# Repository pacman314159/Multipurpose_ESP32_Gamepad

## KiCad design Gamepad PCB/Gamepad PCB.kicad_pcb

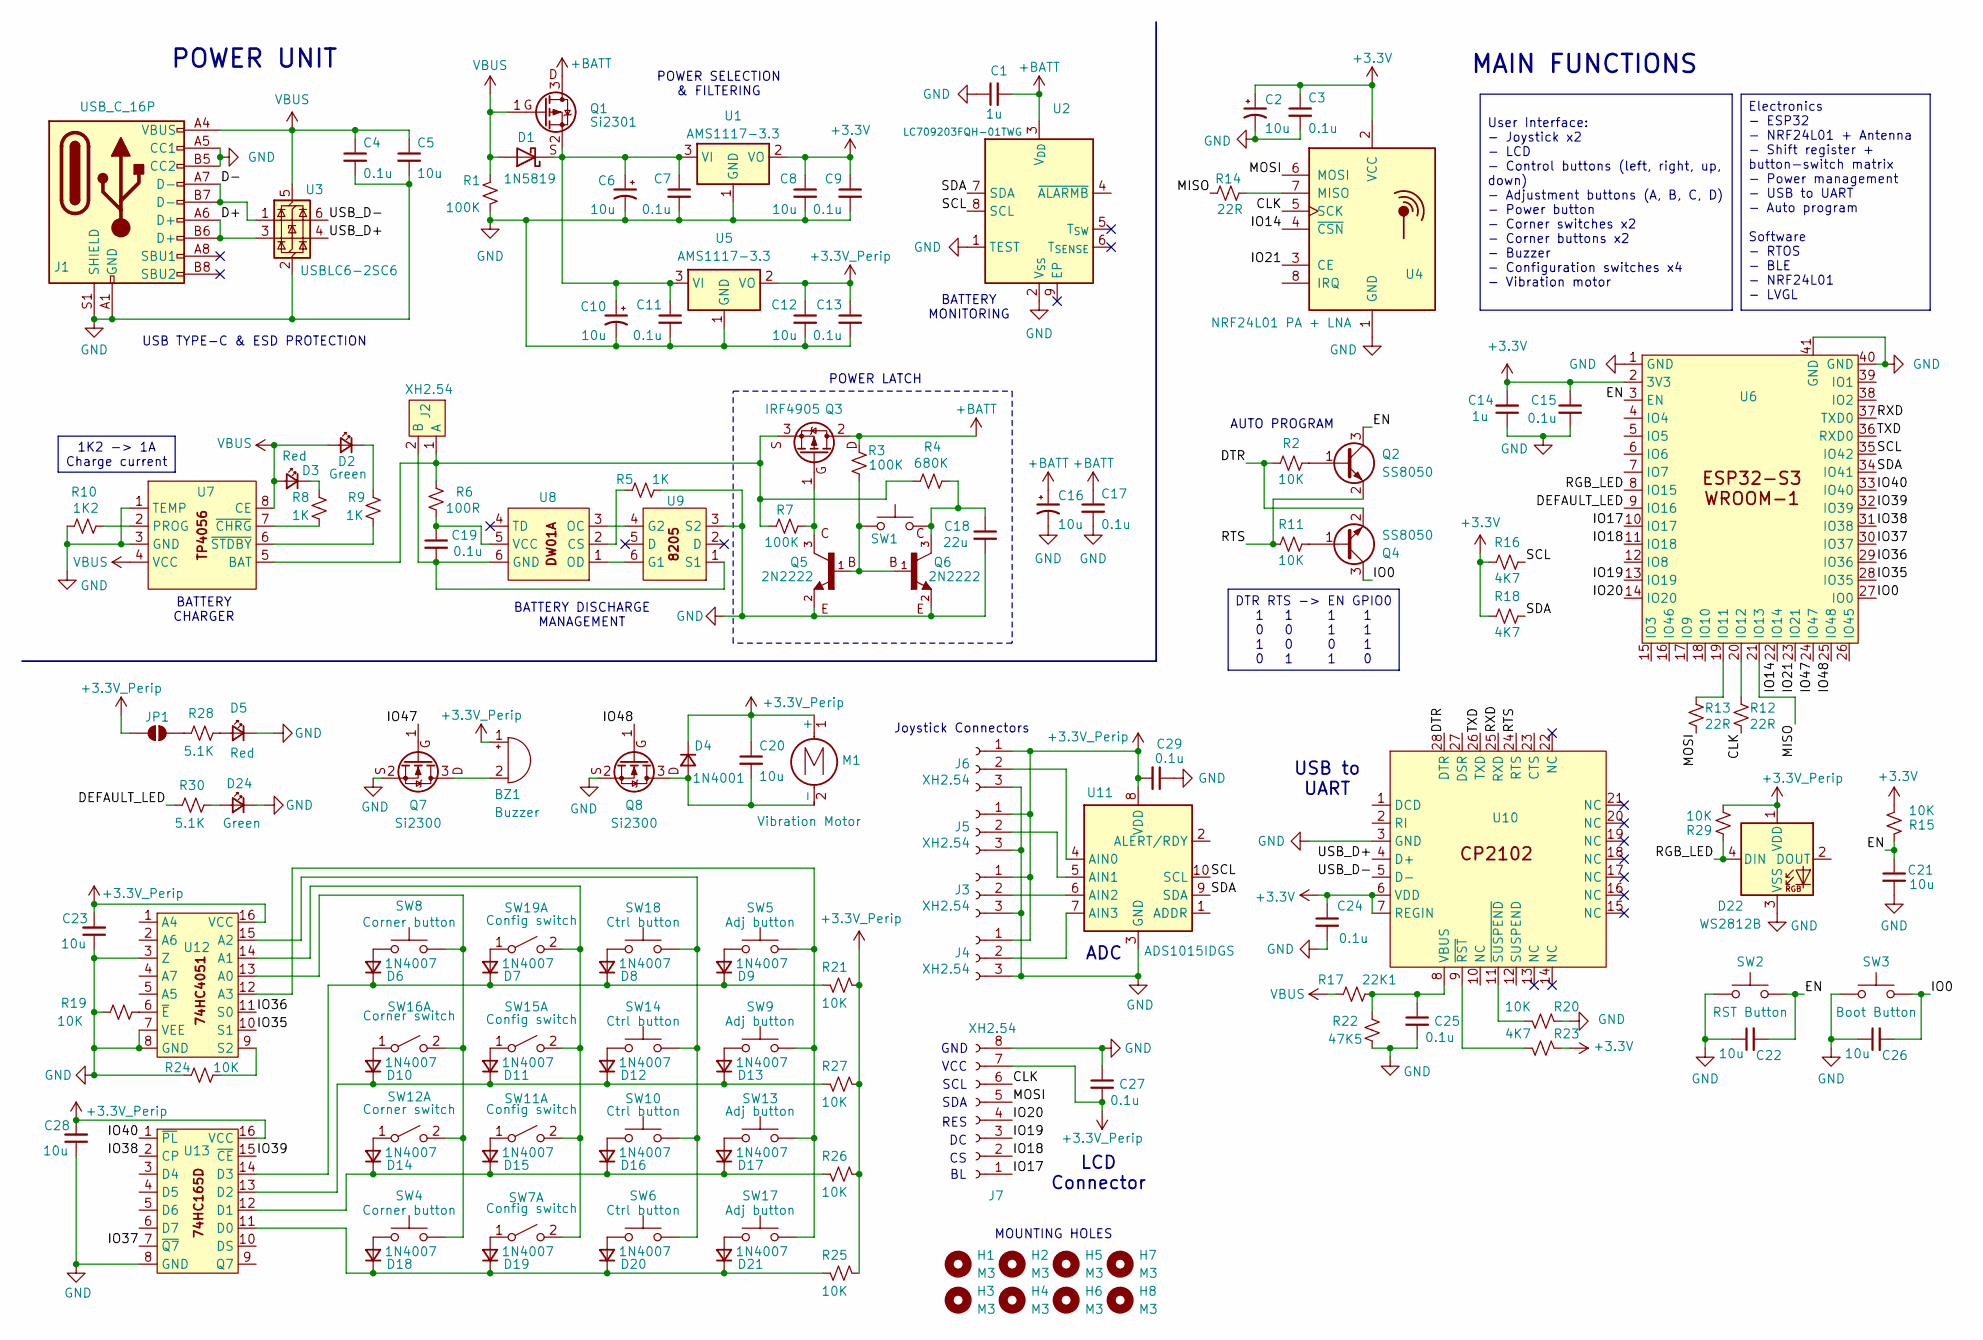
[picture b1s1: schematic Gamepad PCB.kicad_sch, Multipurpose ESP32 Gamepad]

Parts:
BZ1: Buzzer; Buzzer_12x9.5RM7.6
C1, C14: 1u; C_0603_1608Metric_Pad1.08x0.95mm_HandSolder
C2, C6, C10, C16: 10u; C_Radial_D5.0mm_H11.0mm_P2.00mm
C3, C4, C7, C9, C11, C13, C15, C17, C19, C24, C25, C27, C29: 0.1u; C_0603_1608Metric_Pad1.08x0.95mm_HandSolder
C5, C8, C12, C20, C21, C22, C23, C26, C28: 10u; C_0603_1608Metric_Pad1.08x0.95mm_HandSolder
C18: 22u; C_0603_1608Metric_Pad1.08x0.95mm_HandSolder
D1: 1N5819; D_SOD-123
D2, D24: Green; D_1206_3216Metric_Pad1.42x1.75mm_HandSolder
D3, D5: Red; D_1206_3216Metric_Pad1.42x1.75mm_HandSolder
D4: 1N4001; D_SMA_Handsoldering
D6, D7, D8, D9, D10, D11, D12, D13, D14, D15, D16, D17, D18, D19, D20, D21: 1N4007; D_SOD-123
D22: WS2812B; LED_WS2812B_PLCC4_5.0x5.0mm_P3.2mm
H1, H2, H3, H4, H5, H6, H7, H8: M3; MountingHole_3.2mm_M3_DIN965_Pad_TopBottom
J1: USB_C_16P; USB_C_Receptacle_GCT_USB4105-xx-A_16P_TopMnt_Horizontal
J2: XH2.54; 2P_male
J3, J4, J5, J6: XH2.54; 3P_male
J7: XH2.54; 8P_male
JP1: SolderJumper_2_Open; SolderJumper-2_P1.3mm_Open_TrianglePad1.0x1.5mm
M1: Vibration Motor; XDCR_C0720B001F
Q1: Si2301; SOT-23_Handsoldering
Q2, Q4: SS8050; SOT-23_Handsoldering
Q3: IRF4905; TO-220-3_Vertical
Q5, Q6: 2N2222; SOT-23_Handsoldering; PARTREV January 1989
Q7, Q8: Si2300; SOT-23_Handsoldering
R1, R3, R7: 100K; R_0603_1608Metric_Pad0.98x0.95mm_HandSolder
R2, R11, R15, R19, R20, R21, R24, R25, R26, R27, R29: 10K; R_0603_1608Metric_Pad0.98x0.95mm_HandSolder
R4: 680K; R_0603_1608Metric_Pad0.98x0.95mm_HandSolder
R5, R8, R9: 1K; R_0603_1608Metric_Pad0.98x0.95mm_HandSolder
R6: 100R; R_0603_1608Metric_Pad0.98x0.95mm_HandSolder
R10: 1K2; R_0603_1608Metric_Pad0.98x0.95mm_HandSolder
R12, R13, R14: 22R; R_0603_1608Metric_Pad0.98x0.95mm_HandSolder
R16, R18, R23: 4K7; R_0603_1608Metric_Pad0.98x0.95mm_HandSolder
R17: 22K1; R_0603_1608Metric_Pad0.98x0.95mm_HandSolder
R22: 47K5; R_0603_1608Metric_Pad0.98x0.95mm_HandSolder
R28, R30: 5.1K; R_0603_1608Metric_Pad0.98x0.95mm_HandSolder
SW1: SW_Push; SW_Push_6x6mm_SMD
SW2: RST Button; SW_Tactile_SPST_Angled_PTS645Vx31-2LFS
SW3: Boot Button; SW_Tactile_SPST_Angled_PTS645Vx31-2LFS
SW4, SW8: Corner button; SW_Tactile_SPST_Angled_PTS645Vx31-2LFS
SW5, SW9, SW13, SW17: Adj button; SW_Push_6x6mm_SMD
SW6, SW10, SW14, SW18: Ctrl button; SW_Push_6x6mm_SMD
SW7, SW11, SW15, SW19: Config switch; SS12D10
SW12, SW16: Corner switch; MTS102
U1, U5: AMS1117-3.3; SOT-223-3_TabPin2
U2: LC709203FQH-01TWG; WDFN-8-1EP_4x3mm_P0.65mm_EP2.4x1.8mm_ThermalVias
U3: USBLC6-2SC6; SOT-23-6
U4: NRF24L01 PA + LNA; nRF24L01_PA_LNA
U6: ESP32-S3-WROOM1; esp32s3_wroom_1
U7: TP4056; HTSOP-8-1EP_3.9x4.9mm_P1.27mm_EP2.4x3.2mm_ThermalVias
U8: DW01A; TSOT-23-6
U9: 8205; TSOT-23-6
U10: CP2102; QFN-28-1EP_5x5mm_P0.5mm_EP3.1x3.1mm
U11: ADS1015IDGS; MSOP-10-1EP_3x3mm_P0.5mm_EP1.68x1.88mm_ThermalVias
U12: 74HC4051; SOP-16_3.9x9.9mm_P1.27mm
U13: 74HC165D; SOP-16_3.9x9.9mm_P1.27mm

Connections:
+3.3V: C2.1, C3.1, C8.1, C9.1, C14.2, C15.1, C24.1, R15.2, R16.1, R18.1, R23.1, U1.2 (VO), U4.2 (VCC), U6.2 (3V3), U10.6 (VDD), U10.7 (REGIN)
+3.3V_Perip: BZ1.1 (+), C12.1, C13.1, C20.1, C23.2, C27.2, C28.2, C29.2, D4.1 (K), D22.1 (VDD), J3.1, J4.1, J5.1, J6.1, J7.7, JP1.1 (A), M1.1 (+), R21.1, R25.1, R26.1, R27.1, R29.2, U5.2 (VO), U11.8 (VDD), U12.16 (VCC), U13.16 (VCC)
+BATT: C1.2, C16.1, C17.1, Q1.3, Q3.2, R3.1, U2.3 (V_{DD})
/CLK: J7.6, R12.1, U4.5 (SCK)
/D+: J1.A6 (D+), J1.B6 (D+), U3.3 (I/O2)
/D-: J1.A7 (D-), J1.B7 (D-), U3.1 (I/O1)
/DEFAULT_LED: R30.2, U6.9 (IO16)
/DTR: Q4.2 (E), R2.1, U10.28 (DTR)
/EN: C21.1, C22.2, Q2.3 (C), R15.1, SW2.2, U6.3 (EN)
/IO0: C26.2, Q4.3 (C), SW3.2, U6.27 (IO0)
/IO14: U4.4 (~CSN), U6.22 (IO14)
/IO17: J7.1, U6.10 (IO17)
/IO18: J7.2, U6.11 (IO18)
/IO19: J7.3, U6.13 (IO19)
/IO20: J7.4, U6.14 (IO20)
/IO21: U4.3 (CE), U6.23 (IO21)
/IO35: U6.28 (IO35), U12.10 (S1)
/IO36: U6.29 (IO36), U12.11 (S0)
/IO37: U6.30 (IO37), U13.7 (~Q7)
/IO38: U6.31 (IO38), U13.2 (CP)
/IO39: U6.32 (IO39), U13.15 (~CE)
/IO40: U6.33 (IO40), U13.1 (~PL)
/IO47: Q7.1, U6.24 (IO47)
/IO48: Q8.1, U6.25 (IO48)
/MISO: R14.1, U6.21 (IO13)
/MOSI: J7.5, R13.1, U4.6 (MOSI)
/RGB_LED: D22.4 (DIN), R29.1, U6.8 (IO15)
/RTS: Q2.2 (E), R11.1, U10.24 (RTS)
/RXD: U6.37 (TXD0), U10.25 (RXD)
/SCL: R16.2, U2.8 (SCL), U6.35 (IO42), U11.10 (SCL)
/SDA: R18.2, U2.7 (SDA), U6.34 (IO41), U11.9 (SDA)
/TXD: U6.36 (RXD0), U10.26 (TXD)
/USB_D+: U3.4 (I/O2), U10.4 (D+)
/USB_D-: U3.6 (I/O1), U10.5 (D-)
GND: C1.1, C2.2, C3.2, C4.2, C5.2, C6.2, C7.2, C8.2, C9.2, C10.2, C11.2, C12.2, C13.2, C14.1, C15.2, C16.2, C17.2, C18.2, C21.2, C22.1, C23.1, C24.2, C25.2, C26.1, C27.1, C28.1, C29.1, D5.1 (K), D22.3 (VSS), D24.1 (K), J1.A1 (GND), J1.A5 (CC1), J1.A12 (GND), J1.B1 (GND), J1.B5 (CC2), J1.B12 (GND), J1.S1 (SHIELD), J3.3, J4.3, J5.3, J6.3, J7.8, Q5.2, Q6.2, Q7.2, Q8.2, R1.2, R5.2, R10.1, R19.2, R20.1, R22.1, R24.1, SW2.1, SW3.1, U1.1 (GND), U2.1 (TEST), U2.2 (V_{SS}), U3.2 (GND), U4.1 (GND), U5.1 (GND), U6.1 (GND), U6.40 (GND), U6.41 (GND), U7.1 (TEMP), U7.3 (GND), U9.3 (S2), U10.3 (GND), U11.3 (GND), U12.3 (Z), U12.7 (VEE), U12.8 (GND), U13.8 (GND)
unnamed: BZ1.2 (-), Q7.3
unnamed: C18.1, Q6.3, R4.2, SW1.2
unnamed: C6.1, C7.1, C10.1, C11.1, D1.1 (K), Q1.2, U1.3 (VI), U5.3 (VI)
unnamed: D2.1 (K), R9.2
unnamed: D3.1 (K), R8.2
unnamed: C20.2, D4.2 (A), M1.2 (-), Q8.3
unnamed: D5.2 (A), R28.1
unnamed: D6.2 (A), SW8.1
unnamed: D6.1 (K), D7.1 (K), D8.1 (K), D9.1 (K), R21.2, U13.14 (D3)
unnamed: D7.2 (A), SW19.1 (A)
unnamed: D8.2 (A), SW18.1
unnamed: D9.2 (A), SW5.1
unnamed: D10.2 (A), SW16.1 (A)
unnamed: D10.1 (K), D11.1 (K), D12.1 (K), D13.1 (K), R27.2, U13.13 (D2)
unnamed: D11.2 (A), SW15.1 (A)
unnamed: D12.2 (A), SW14.1
unnamed: D13.2 (A), SW9.1
unnamed: D14.2 (A), SW12.1 (A)
unnamed: D14.1 (K), D15.1 (K), D16.1 (K), D17.1 (K), R26.2, U13.12 (D1)
unnamed: D15.2 (A), SW11.1 (A)
unnamed: D16.2 (A), SW10.1
unnamed: D17.2 (A), SW13.1
unnamed: D18.2 (A), SW4.2
unnamed: D18.1 (K), D19.1 (K), D20.1 (K), D21.1 (K), R25.2, U13.11 (D0)
unnamed: D19.2 (A), SW7.1 (A)
unnamed: D20.2 (A), SW6.1
unnamed: D21.2 (A), SW17.1
unnamed: D24.2 (A), R30.1
unnamed: J2.1 (A), Q3.3, R4.1, R6.2, R7.2, U7.5 (BAT)
unnamed: C19.2, J2.2 (B), U8.6 (GND), U9.1 (S1)
unnamed: J3.2, U11.6 (AIN2)
unnamed: J4.2, U11.7 (AIN3)
unnamed: J5.2, U11.5 (AIN1)
unnamed: J6.2, U11.4 (AIN0)
unnamed: JP1.2 (B), R28.2
unnamed: Q2.1 (B), R2.2
unnamed: Q3.1, Q5.3, R7.1
unnamed: Q4.1 (B), R11.2
unnamed: Q5.1, Q6.1, R3.2, SW1.1
unnamed: SW7.2 (B), SW11.2 (B), SW15.2 (B), SW19.2 (B), U12.14 (A1)
unnamed: SW4.1, SW8.2, SW12.2 (B), SW16.2 (B), U12.13 (A0)
unnamed: R14.2, U4.7 (MISO)
unnamed: R13.2, U6.19 (IO11)
unnamed: R12.2, U6.20 (IO12)
unnamed: R10.2, U7.2 (PROG)
unnamed: R8.1, U7.7 (~CHRG)
unnamed: R9.1, U7.6 (~STDBY)
unnamed: R5.1, U8.2 (CS)
unnamed: U8.3 (OC), U9.4 (G2)
unnamed: U8.1 (OD), U9.6 (G1)
unnamed: C19.1, R6.1, U8.5 (VCC)
unnamed: C25.1, R17.2, R22.2, U10.8 (VBUS)
unnamed: R23.2, U10.9 (~RST)
unnamed: R20.2, U10.11 (~SUSPEND)
unnamed: SW6.2, SW10.2, SW14.2, SW18.2, U12.15 (A2)
unnamed: SW5.2, SW9.2, SW13.2, SW17.2, U12.12 (A3)
unnamed: R24.2, U12.9 (S2)
unnamed: R19.1, U12.6 (~E)
VBUS: C4.1, C5.1, D1.2 (A), D2.2 (A), D3.2 (A), J1.A4 (VBUS), J1.A9 (VBUS), J1.B4 (VBUS), J1.B9 (VBUS), Q1.1, R1.1, R17.1, U3.5 (VBUS), U7.4 (VCC), U7.8 (CE)

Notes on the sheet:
MAIN FUNCTIONS
POWER UNIT
BATTERY DISCHARGE MANAGEMENT
BATTERY CHARGER
USB to UART
BATTERY MONITORING
LCD Connector
RES
MOUNTING HOLES
ADC
VCC
POWER SELECTION & FILTERING
AUTO PROGRAM
SDA
USB TYPE-C & ESD PROTECTION
POWER LATCH
GND
Joystick Connectors
SCL
DTR RTS -> EN GPIO0 1 1 1 1 0 0 1 1 1 0 0 1 0 1 1 0
1K2 -> 1A Charge current
Electronics - ESP32 - NRF24L01 + Antenna - Shift register + button-switch matrix - Power management - USB to UART - Auto program Software - RTOS - BLE - NRF24L01 - LVGL
User Interface: - Joystick x2 - LCD - Control buttons (left, right, up, down) - Adjustment buttons (A, B, C, D) - Power button - Corner switches x2 - Corner buttons x2 - Buzzer - Configuration switches x4 - Vibration motor

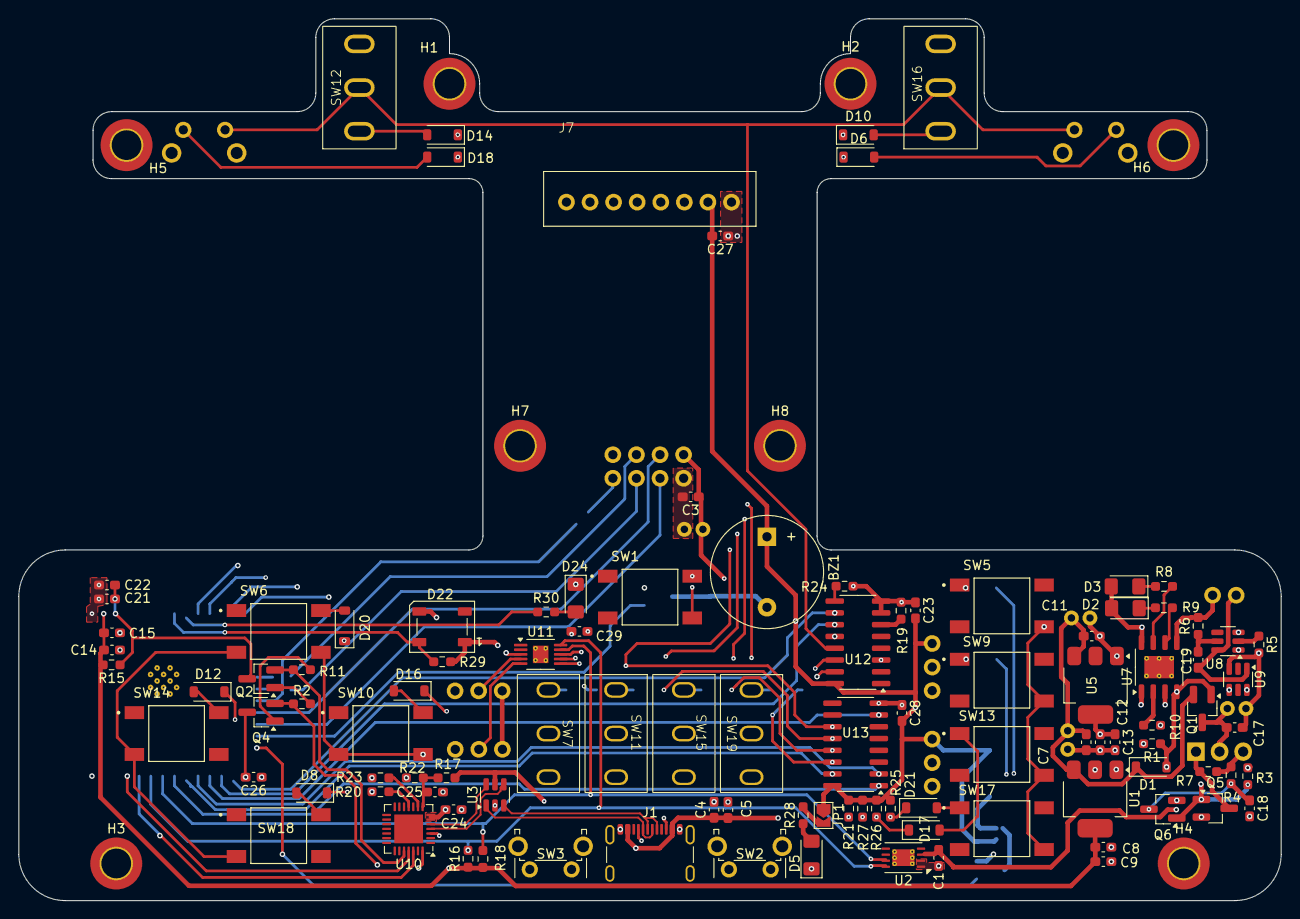
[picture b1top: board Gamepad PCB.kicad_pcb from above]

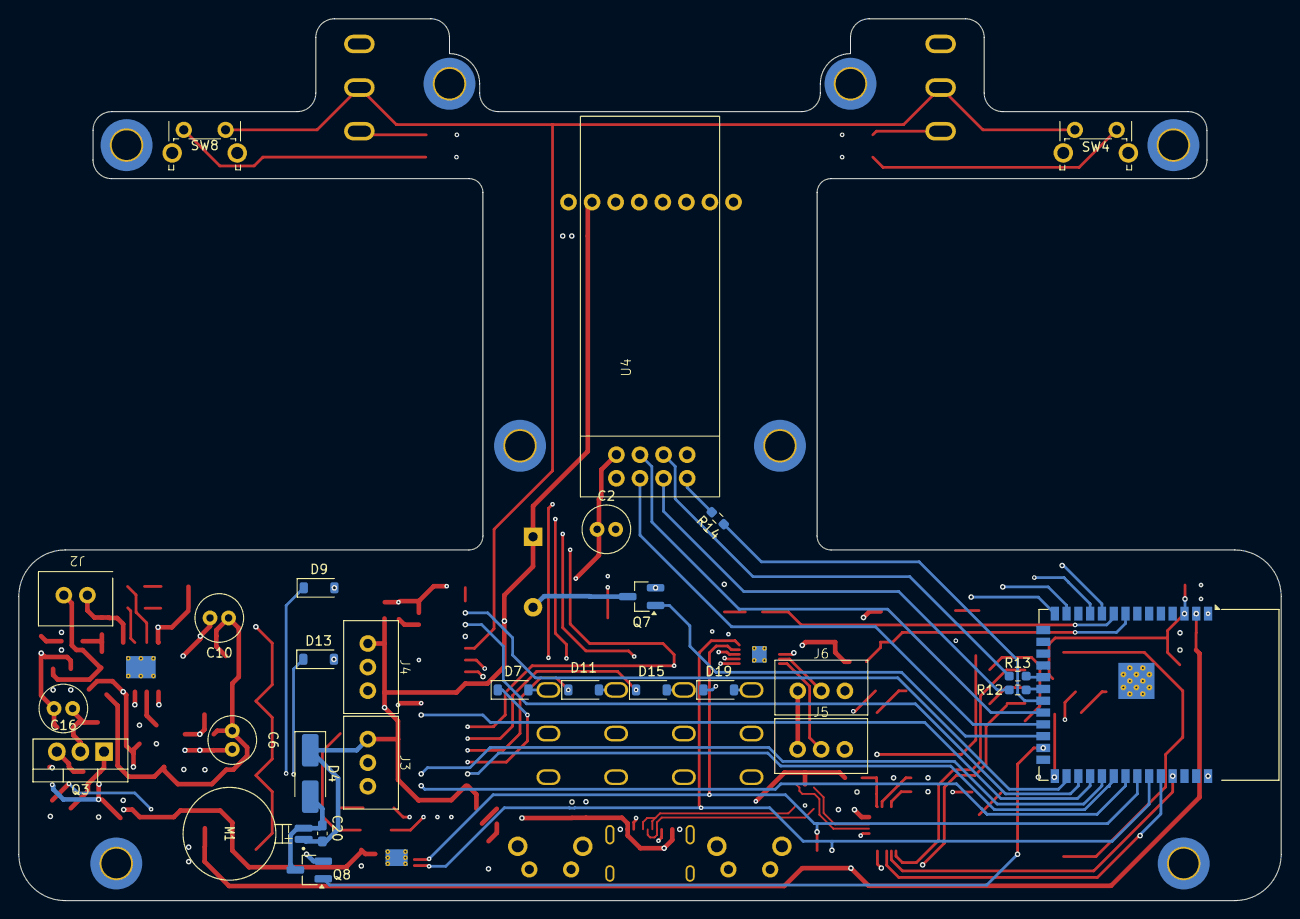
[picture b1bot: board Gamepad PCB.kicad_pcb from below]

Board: 4 copper layers, 136.0 x 95.0 mm, 140 parts (28 on the bottom side), 94 nets.

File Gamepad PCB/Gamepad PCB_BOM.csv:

"Reference","Qty","Value","Footprint","Price","Description"
"BZ1","1","Buzzer","Buzzer_Beeper:Buzzer_12x9.5RM7.6","2500","https://icdayroi.com/buzzer-12095-5v"
"C1,C14","2","1u","Capacitor_SMD:C_0603_1608Metric_Pad1.08x0.95mm_HandSolder","400","https://icdayroi.com/tu-dien-1uf-50v-0603"
"C2,C6,C10,C16","4","10u","Capacitor_THT:C_Radial_D5.0mm_H11.0mm_P2.00mm","250","https://icdayroi.com/tu-hoa-10uf50v"
"C3,C4,C7,C9,C11,C13,C15,C17,C19,C24,C25,C27","12","0.1u","Capacitor_SMD:C_0603_1608Metric_Pad1.08x0.95mm_HandSolder","200","https://icdayroi.com/tu-dien-100nf-50v-0603"
"C5,C8,C12,C20,C21,C22,C23,C26,C28","9","10u","Capacitor_SMD:C_0603_1608Metric_Pad1.08x0.95mm_HandSolder","400","https://icdayroi.com/tu-dien-10uf-25v-0603"
"C18","1","22u","Capacitor_SMD:C_0603_1608Metric_Pad1.08x0.95mm_HandSolder","200","https://icdayroi.com/tu-dien-100nf-50v-0603"
"D1","1","1N5819","Diode_SMD:D_SOD-123","300","https://icdayroi.com/diode-1n5819-sod123-size-1206"
"D2","1","Green","Diode_SMD:D_1206_3216Metric_Pad1.42x1.75mm_HandSolder","840","https://icdayroi.com/led-mau-xanh-la-1206"
"D3,D5","2","Red","Diode_SMD:D_1206_3216Metric_Pad1.42x1.75mm_HandSolder","736","https://icdayroi.com/led-mau-xanh-la-1206"
"D4","1","1N4001","Diode_SMD:D_SMA_Handsoldering","200","https://icdayroi.com/1n4001-m1"
"H1,H2,H3,H4,H5,H6,H7,H8","8","M3","MountingHole:MountingHole_3.2mm_M3_DIN965_Pad_TopBottom","",""
"J1","1","USB_C_16P","Connector_USB:USB_C_Receptacle_GCT_USB4105-xx-A_16P_TopMnt_Horizontal","3000","https://icdayroi.com/usb-3-1-type-c-female-socket"
"J2","1","XH2.54","XH_2p54:2P_male","210","https://chipn24.com/10-cai-f297-header-2p-xh2-54-2p-duc-than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"
"J3,J4,J5,J6","4","XH2.54","XH_2p54:3P_male","320","https://chipn24.com/10-cai-f297-header-3p-xh2-54-3p-duc-than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"
"J7","1","XH2.54","XH_2p54:8P_male","840","https://chipn24.com/10-cai-f297-header-8p-xh2-54-8p-duc-than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"
"JP1","1","SolderJumper_2_Open","Jumper:SolderJumper-2_P1.3mm_Open_TrianglePad1.0x1.5mm","",""
"M1","1","Vibration Motor","Coin_Vibration_Motor:XDCR_C0720B001F","7000","https://icdayroi.com/dong-co-rung-1027"
"Q1","1","Si2301","Package_TO_SOT_SMD:SOT-23_Handsoldering","450","https://icdayroi.com/si2301ds"
"Q2,Q4","2","SS8050","Package_TO_SOT_SMD:SOT-23_Handsoldering","400","https://icdayroi.com/s8050"
"Q3","1","IRF4905","Package_TO_SOT_THT:TO-220-3_Vertical","24000","https://icdayroi.com/irf4905pbf-mosfet-p-ch-to-220-55v-74a"
"Q5,Q6","2","2N2222","Package_TO_SOT_SMD:SOT-23_Handsoldering","632","https://chipn24.com/25-con-g3-1-transistor-dan-2n2222-1p-sot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"
"Q7,Q8","2","Si2300","Package_TO_SOT_SMD:SOT-23_Handsoldering","400","https://icdayroi.com/si2300ds"
"R1,R3,R7","3","100K","Resistor_SMD:R_0603_1608Metric_Pad0.98x0.95mm_HandSolder","40","https://icdayroi.com/dien-tro-100k-0603-1-goi-50-con"
"R2,R11,R15,R19,R20,R21,R24,R25,R26,R27","10","10K","Resistor_SMD:R_0603_1608Metric_Pad0.98x0.95mm_HandSolder","40","https://icdayroi.com/dien-tro-10k-0603-1-goi-50-con"
"R4","1","680K","Resistor_SMD:R_0603_1608Metric_Pad0.98x0.95mm_HandSolder","40","https://icdayroi.com/dien-tro-680k-0603-1-goi-50-con"
"R5,R8,R9,R28","4","1K","Resistor_SMD:R_0603_1608Metric_Pad0.98x0.95mm_HandSolder","40","https://icdayroi.com/dien-tro-1k-0603-1-goi-50-con"
"R6","1","100R","Resistor_SMD:R_0603_1608Metric_Pad0.98x0.95mm_HandSolder","40","https://icdayroi.com/dien-tro-100ohm-0603-1-goi-50-con"
"R10","1","1K2","Resistor_SMD:R_0603_1608Metric_Pad0.98x0.95mm_HandSolder","40","https://icdayroi.com/dien-tro-1-2k-0603-1-goi-50-con"
"R12,R13,R14","3","22R","Resistor_SMD:R_0603_1608Metric_Pad0.98x0.95mm_HandSolder","84","https://chipn24.com/50-con-g43-dien-tro-dan-smd-0603-22r-1-k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"
"R16,R18,R23","3","4K7","Resistor_SMD:R_0603_1608Metric_Pad0.98x0.95mm_HandSolder","40","https://icdayroi.com/dien-tro-4k7-0603-1-goi-50-con"
"R17","1","22K1","Resistor_SMD:R_0603_1608Metric_Pad0.98x0.95mm_HandSolder","40","https://icdayroi.com/dien-tro-22k-0603-1-goi-50-con"
"R22","1","47K5","Resistor_SMD:R_0603_1608Metric_Pad0.98x0.95mm_HandSolder","40","https://icdayroi.com/dien-tro-47k-0603-1-goi-50-con"
"SW1","1","SW_Push","SW_Push_6x6mm_SMD:SW_Push_6x6mm_SMD","530","https://chipn24.com/10-cai-k77-nut-nhan-4-chan-dan-smd-6x6x6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"
"SW2","1","RST Button","Button_Switch_THT:SW_Tactile_SPST_Angled_PTS645Vx31-2LFS","1000","https://chipn24.com/10-cai-f64-nut-nhan-4-chan-vuong-cong-6x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"
"SW3","1","Boot Button","Button_Switch_THT:SW_Tactile_SPST_Angled_PTS645Vx31-2LFS","1000","https://chipn24.com/10-cai-f64-nut-nhan-4-chan-vuong-cong-6x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"
"SW4,SW8","2","Corner button","Button_Switch_THT:SW_Tactile_SPST_Angled_PTS645Vx31-2LFS","1000","https://chipn24.com/10-cai-f64-nut-nhan-4-chan-vuong-cong-6x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"
"SW5,SW9,SW13,SW17","4","Adj button","SW_Push_6x6mm_SMD:SW_Push_6x6mm_SMD","530","https://chipn24.com/10-cai-k77-nut-nhan-4-chan-dan-smd-6x6x6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"
"SW6,SW10,SW14,SW18","4","Ctrl button","SW_Push_6x6mm_SMD:SW_Push_6x6mm_SMD","530","https://chipn24.com/10-cai-k77-nut-nhan-4-chan-dan-smd-6x6x6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"
"SW7,SW11,SW15,SW19","4","Config switch","SW_SS12:SS12D10","4200","https://chipn24.com/k88-cong-tac-gat-ss12d10-4-7mm-3-chan-2-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"
"SW12,SW16","2","Corner switch","SW_MTS102:MTS102","6300","https://chipn24.com/f101-1-cong-tac-mts-102-mts102-cong-tac-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"
"U1,U5","2","AMS1117-3.3","Package_TO_SOT_SMD:SOT-223-3_TabPin2","900","https://icdayroi.com/ams1117-3-3v"
"U2","1","LC709203FQH-01TWG","Package_DFN_QFN:WDFN-8-1EP_4x3mm_P0.65mm_EP2.4x1.8mm_ThermalVias","45000","https://detail.tmall.com/item.htm?abbucket=7&detail_redpacke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"
"U3","1","USBLC6-2SC6","Package_TO_SOT_SMD:SOT-23-6","4000","https://icdayroi.com/usblc6-2sc6-tvs-diode-5-25v-17v-sot23-6"
"U4","1","NRF24L01 PA + LNA","RF_Module:nRF24L01_PA_LNA","43500","https://www.thegioiic.com/nrf24l01-pa-lna-mach-thu-phat-rf-2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"
"U6","1","ESP32-S3-WROOM1","ESP32_modules:esp32s3_wroom_1","135000","https://hshop.vn/mach-thu-phat-wifi-ble-soc-esp32-s3-esp32-s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"
"U7","1","TP4056","Package_SO:SOP-8-1EP_4.57x4.57mm_P1.27mm_EP4.57x4.45mm","3000","https://icdayroi.com/tp4056"
"U8","1","DW01A","Package_TO_SOT_SMD:TSOT-23-6","1000","https://icdayroi.com/dw01a"
"U9","1","8205","Package_TO_SOT_SMD:TSOT-23-6","800","https://icdayroi.com/fs8205a-n-mosfet-sot23-6"
"U10","1","CP2102","Package_DFN_QFN:QFN-28-1EP_5x5mm_P0.5mm_EP3.1x3.1mm","65000","https://icdayroi.com/cp2102-qfn28"
"U11","1","ADS1015IDGS","Package_SO:MSOP-10-1EP_3x3mm_P0.5mm_EP1.68x1.88mm_ThermalVias","10200","https://item.taobao.com/item.htm?detail_redpacket_pop=true&i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"
"U12","1","74HC4051","Package_SO:SOP-16_3.9x9.9mm_P1.27mm","9500","https://chipn24.com/sop-ic-dan-744051-74hc4051-sop-16-hang-t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"
"U13","1","74HC165D","Package_SO:SOP-16_3.9x9.9mm_P1.27mm","4200","https://chipn24.com/sop-ic-dan-74165-74hc165-sop-16-smd-74hc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"

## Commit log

2025-07-30 add imgs
2025-08-01 setup tools, libs needed for firmware
2025-08-07 fix Q3, R14, C18 schematic
2025-08-07 fix gitignore
2025-08-13 fix entire pcb
2025-08-14 add pcb interface
